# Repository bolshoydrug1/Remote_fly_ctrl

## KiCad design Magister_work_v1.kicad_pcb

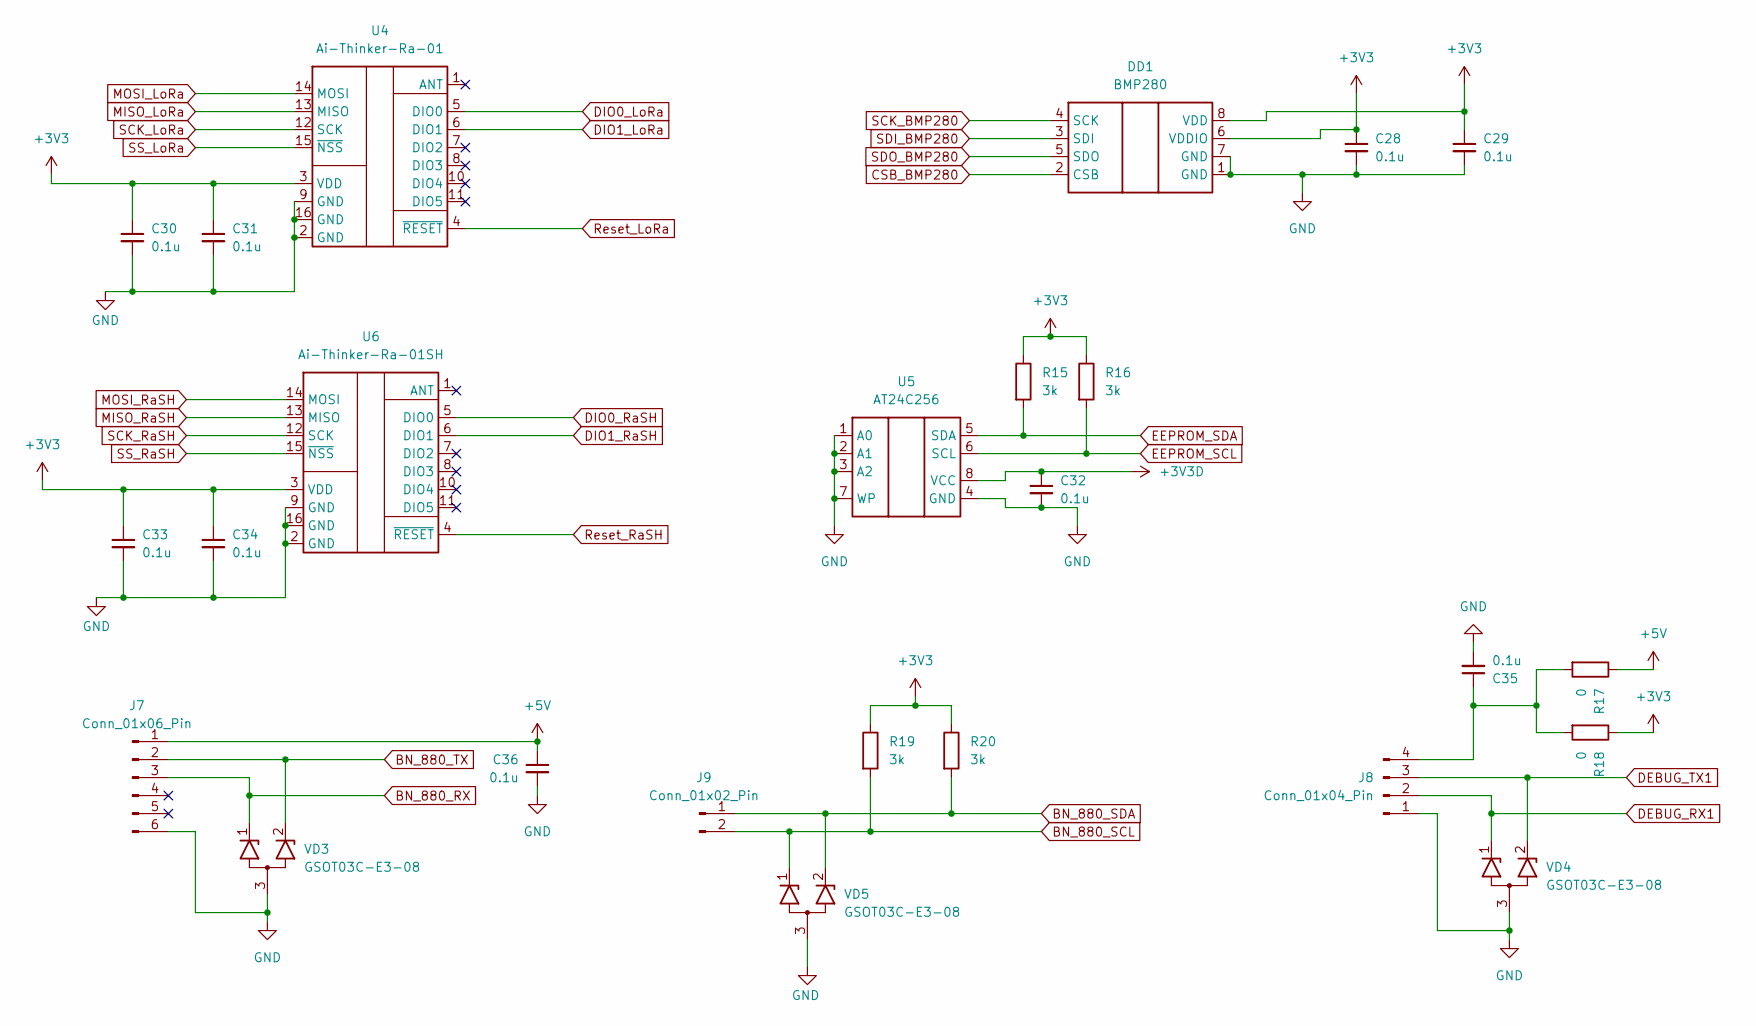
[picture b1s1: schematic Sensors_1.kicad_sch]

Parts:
C28, C29, C30, C31, C32, C33, C34, C35, C36: 0.1u; C_0805_2012Metric_Pad1.18x1.45mm_HandSolder
DD1: BMP280; Bosch_LGA-8_2x2.5mm_P0.65mm_ClockwisePinNumbering
J7: Conn_01x06_Pin; Hirose_DF13-06P-1.25DSA_1x06_P1.25mm_Vertical
J8: Conn_01x04_Pin; PinSocket_1x04_P2.54mm_Vertical
J9: Conn_01x02_Pin; Hirose_DF13-02P-1.25DSA_1x02_P1.25mm_Vertical
R15, R16, R19, R20: 3k; R_0805_2012Metric_Pad1.20x1.40mm_HandSolder
R17, R18: 0; R_0805_2012Metric_Pad1.20x1.40mm_HandSolder
U4: Ai-Thinker-Ra-01; Ai-Thinker-Ra-01-LoRa
U5: AT24C256; SOIC-8_3.9x4.9mm_P1.27mm
U6: Ai-Thinker-Ra-01SH; Ai-Thinker-Ra-01-LoRa
VD3, VD4, VD5: GSOT03C-E3-08; SOT-23

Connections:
+3V3: C28.1, C29.1, C30.1, C31.1, C32.1, C33.1, C34.1, DD1.6 (VDDIO), DD1.8 (VDD), R15.1, R16.1, R18.1, R19.1, R20.1, U4.3 (VDD), U5.8 (VCC), U6.3 (VDD); also elsewhere on the board
+5V: C36.1, J7.1, R17.1; also elsewhere on the board
BN_880_RX: J7.3, VD3.1 (K1); also elsewhere on the board
BN_880_SCL: J9.2, R19.2, VD5.1 (K1); also elsewhere on the board
BN_880_SDA: J9.1, R20.2, VD5.2 (K2); also elsewhere on the board
BN_880_TX: J7.2, VD3.2 (K2); also elsewhere on the board
CSB_BMP280: DD1.2 (CSB); also elsewhere on the board
DEBUG_RX1: J8.2, VD4.1 (K1); also elsewhere on the board
DEBUG_TX1: J8.3, VD4.2 (K2); also elsewhere on the board
DIO0_LoRa: U4.5 (DIO0); also elsewhere on the board
DIO0_RaSH: U6.5 (DIO0); also elsewhere on the board
DIO1_LoRa: U4.6 (DIO1); also elsewhere on the board
DIO1_RaSH: U6.6 (DIO1); also elsewhere on the board
EEPROM_SCL: R16.2, U5.6 (SCL); also elsewhere on the board
EEPROM_SDA: R15.2, U5.5 (SDA); also elsewhere on the board
GND: C28.2, C29.2, C30.2, C31.2, C32.2, C33.2, C34.2, C35.2, C36.2, DD1.1 (GND), DD1.7 (GND), J7.6, J8.1, U4.2 (GND), U4.9 (GND), U4.16 (GND), U5.1 (A0), U5.2 (A1), U5.3 (A2), U5.4 (GND), U5.7 (WP), U6.2 (GND), U6.9 (GND), U6.16 (GND), VD3.3 (A), VD4.3 (A), VD5.3 (A); also elsewhere on the board
MISO_LoRa: U4.13 (MISO); also elsewhere on the board
MISO_RaSH: U6.13 (MISO); also elsewhere on the board
MOSI_LoRa: U4.14 (MOSI); also elsewhere on the board
MOSI_RaSH: U6.14 (MOSI); also elsewhere on the board
unnamed: C35.1, J8.4, R17.2, R18.2
Reset_LoRa: U4.4 (~RESET); also elsewhere on the board
Reset_RaSH: U6.4 (~RESET); also elsewhere on the board
SCK_BMP280: DD1.4 (SCK); also elsewhere on the board
SCK_LoRa: U4.12 (SCK); also elsewhere on the board
SCK_RaSH: U6.12 (SCK); also elsewhere on the board
SDI_BMP280: DD1.3 (SDI); also elsewhere on the board
SDO_BMP280: DD1.5 (SDO); also elsewhere on the board
SS_LoRa: U4.15 (~NSS); also elsewhere on the board
SS_RaSH: U6.15 (~NSS); also elsewhere on the board

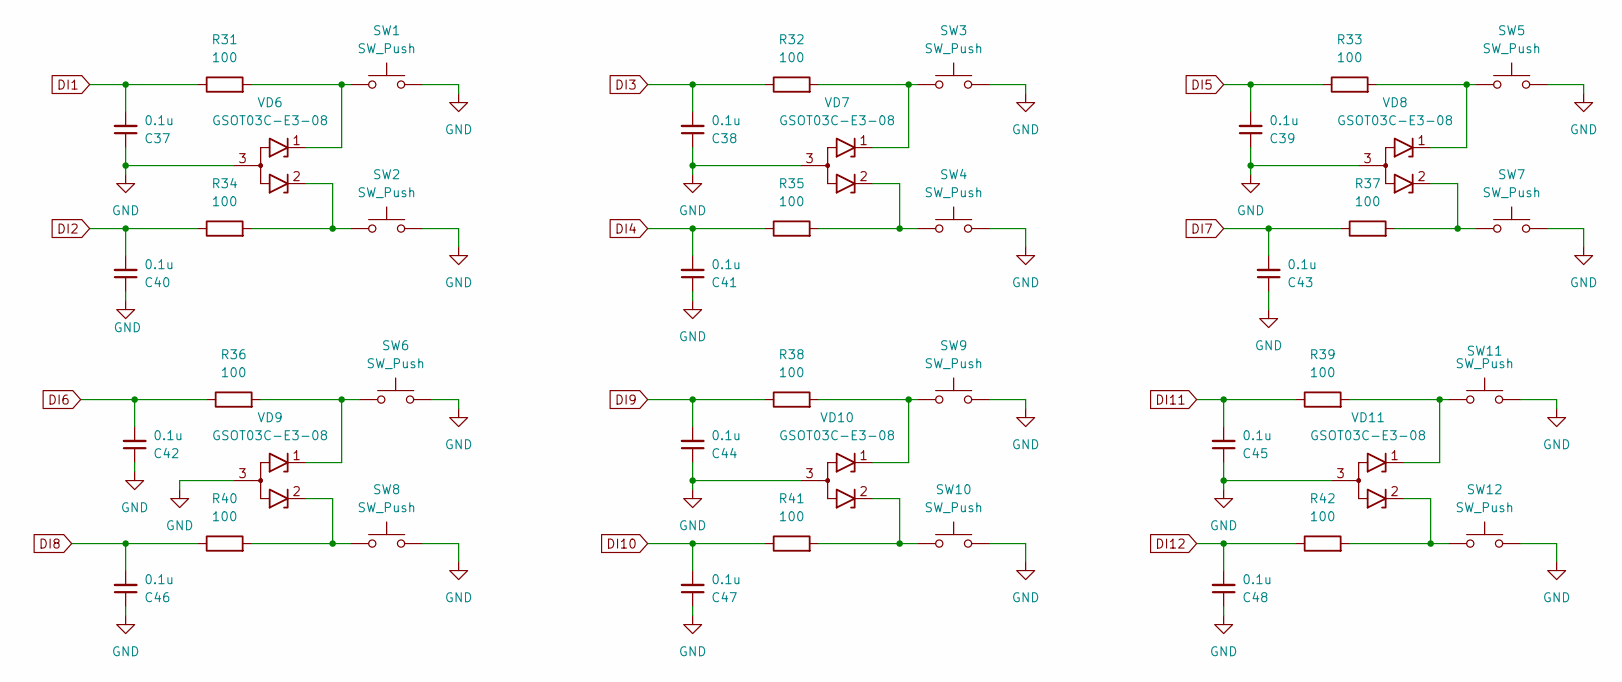
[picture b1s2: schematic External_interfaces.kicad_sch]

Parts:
C37, C38, C39, C40, C41, C42, C43, C44, C45, C46, C47, C48: 0.1u; C_0805_2012Metric_Pad1.18x1.45mm_HandSolder
R31, R32, R33, R34, R35, R36, R37, R38, R39, R40, R41, R42: 100; R_0805_2012Metric_Pad1.20x1.40mm_HandSolder
SW1, SW2, SW3, SW4, SW5, SW6, SW7, SW8, SW9, SW10, SW11, SW12: SW_Push; SW_PUSH_6mm
VD6, VD7, VD8, VD9, VD10, VD11: GSOT03C-E3-08; SOT-23

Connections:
DI1: C37.2, R31.1; also elsewhere on the board
DI2: C40.2, R34.1; also elsewhere on the board
DI3: C38.2, R32.1; also elsewhere on the board
DI4: C41.2, R35.1; also elsewhere on the board
DI5: C39.2, R33.1; also elsewhere on the board
DI6: C42.2, R36.1; also elsewhere on the board
DI7: C43.2, R37.1; also elsewhere on the board
DI8: C46.2, R40.1; also elsewhere on the board
DI9: C44.2, R38.1; also elsewhere on the board
DI10: C47.2, R41.1; also elsewhere on the board
DI11: C45.2, R39.1; also elsewhere on the board
DI12: C48.2, R42.1; also elsewhere on the board
GND: C37.1, C38.1, C39.1, C40.1, C41.1, C42.1, C43.1, C44.1, C45.1, C46.1, C47.1, C48.1, SW1.2, SW2.2, SW3.2, SW4.2, SW5.2, SW6.2, SW7.2, SW8.2, SW9.2, SW10.2, SW11.2, SW12.2, VD6.3 (A), VD7.3 (A), VD8.3 (A), VD9.3 (A), VD10.3 (A), VD11.3 (A); also elsewhere on the board
unnamed: R31.2, SW1.1, VD6.1 (K1)
unnamed: R34.2, SW2.1, VD6.2 (K2)
unnamed: R32.2, SW3.1, VD7.1 (K1)
unnamed: R35.2, SW4.1, VD7.2 (K2)
unnamed: R33.2, SW5.1, VD8.1 (K1)
unnamed: R37.2, SW7.1, VD8.2 (K2)
unnamed: R36.2, SW6.1, VD9.1 (K1)
unnamed: R40.2, SW8.1, VD9.2 (K2)
unnamed: R38.2, SW9.1, VD10.1 (K1)
unnamed: R41.2, SW10.1, VD10.2 (K2)
unnamed: R39.2, SW11.1, VD11.1 (K1)
unnamed: R42.2, SW12.1, VD11.2 (K2)

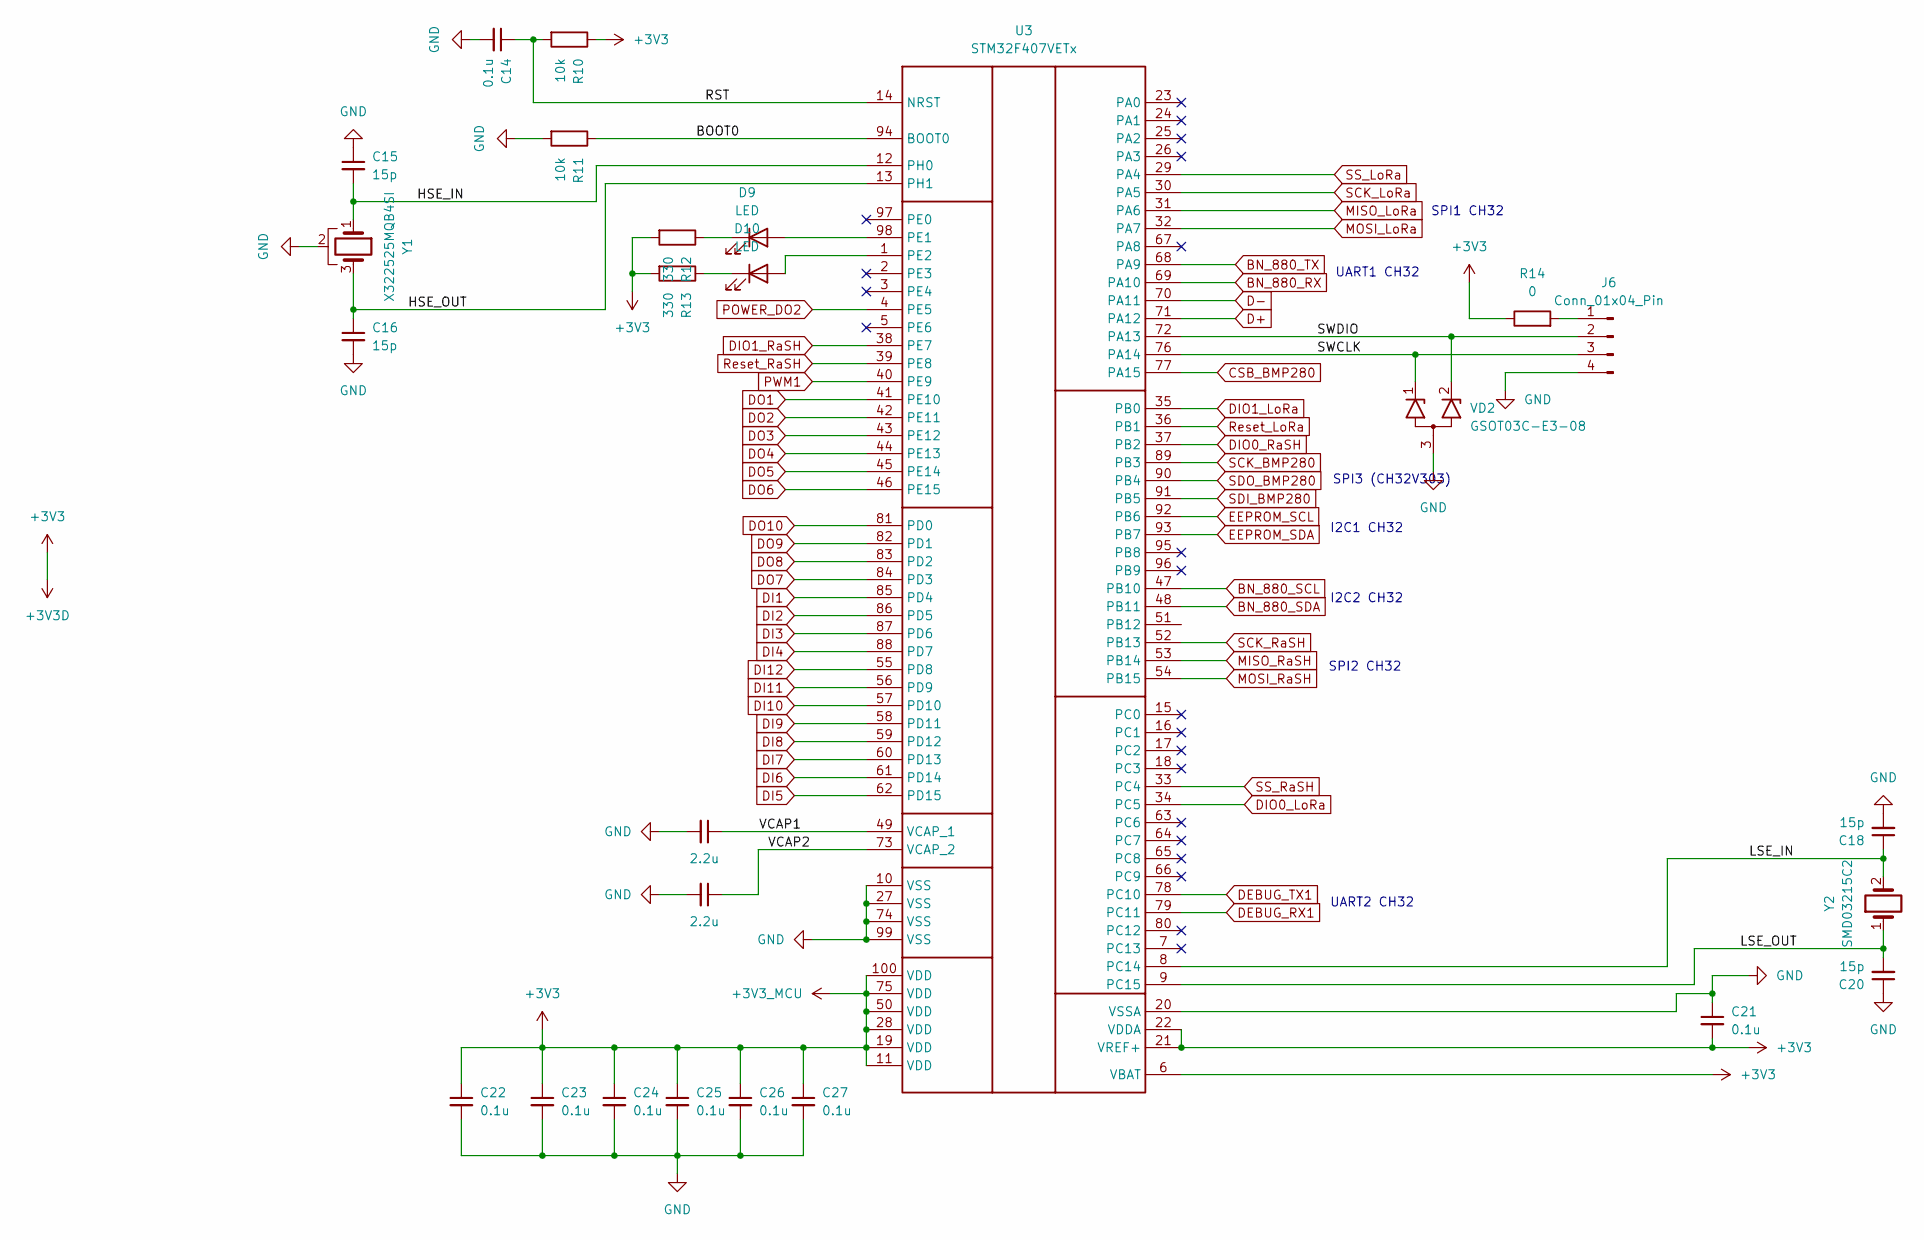
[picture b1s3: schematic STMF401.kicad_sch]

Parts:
C14, C21, C22, C23, C24, C25, C26, C27: 0.1u; C_0805_2012Metric_Pad1.18x1.45mm_HandSolder
C15, C16, C18, C20: 15p; C_0805_2012Metric_Pad1.18x1.45mm_HandSolder
C17, C19: 2.2u; C_0805_2012Metric_Pad1.18x1.45mm_HandSolder
D9, D10: LED; LED_0805_2012Metric_Pad1.15x1.40mm_HandSolder
J6: Conn_01x04_Pin; PinSocket_1x04_P2.54mm_Vertical
R10, R11: 10k; R_0805_2012Metric_Pad1.20x1.40mm_HandSolder
R12, R13: 330; R_0805_2012Metric_Pad1.20x1.40mm_HandSolder
R14: 0; R_0805_2012Metric_Pad1.20x1.40mm_HandSolder
U3: STM32F407VETx; LQFP-100_14x14mm_P0.5mm
VD2: GSOT03C-E3-08; SOT-23
Y1: X322525MQB4SI; Oscillator_SMD_Abracon_ASE-4Pin_3.2x2.5mm
Y2: SMD03215C2; Crystal_SMD_3215-2Pin_3.2x1.5mm

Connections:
+3V3: C21.2, C22.1, C23.1, C24.1, C25.1, C26.1, C27.1, R10.1, R12.2, R13.2, R14.1, U3.6 (VBAT), U3.11 (VDD), U3.19 (VDD), U3.21 (VREF+), U3.22 (VDDA), U3.28 (VDD), U3.50 (VDD), U3.75 (VDD), U3.100 (VDD); also elsewhere on the board
/STMF401_Sheet/BOOT0: R11.1, U3.94 (BOOT0)
/STMF401_Sheet/HSE_IN: C15.2, U3.12 (PH0), Y1.1 (OSC)
/STMF401_Sheet/HSE_OUT: C16.1, U3.13 (PH1), Y1.3 (OSC)
/STMF401_Sheet/LSE_IN: C18.1, U3.8 (PC14), Y2.2 (OSC)
/STMF401_Sheet/LSE_OUT: C20.2, U3.9 (PC15), Y2.1 (OSC)
/STMF401_Sheet/RST: C14.1, R10.2, U3.14 (NRST)
/STMF401_Sheet/SWCLK: J6.3, U3.76 (PA14), VD2.1 (K1)
/STMF401_Sheet/SWDIO: J6.2, U3.72 (PA13), VD2.2 (K2)
/STMF401_Sheet/VCAP1: C17.1, U3.49 (VCAP_1)
/STMF401_Sheet/VCAP2: C19.1, U3.73 (VCAP_2)
BN_880_RX: U3.69 (PA10); also elsewhere on the board
BN_880_SCL: U3.47 (PB10); also elsewhere on the board
BN_880_SDA: U3.48 (PB11); also elsewhere on the board
BN_880_TX: U3.68 (PA9); also elsewhere on the board
CSB_BMP280: U3.77 (PA15); also elsewhere on the board
D+: U3.71 (PA12); also elsewhere on the board
D-: U3.70 (PA11); also elsewhere on the board
DEBUG_RX1: U3.79 (PC11); also elsewhere on the board
DEBUG_TX1: U3.78 (PC10); also elsewhere on the board
DI1: U3.85 (PD4); also elsewhere on the board
DI2: U3.86 (PD5); also elsewhere on the board
DI3: U3.87 (PD6); also elsewhere on the board
DI4: U3.88 (PD7); also elsewhere on the board
DI5: U3.62 (PD15); also elsewhere on the board
DI6: U3.61 (PD14); also elsewhere on the board
DI7: U3.60 (PD13); also elsewhere on the board
DI8: U3.59 (PD12); also elsewhere on the board
DI9: U3.58 (PD11); also elsewhere on the board
DI10: U3.57 (PD10); also elsewhere on the board
DI11: U3.56 (PD9); also elsewhere on the board
DI12: U3.55 (PD8); also elsewhere on the board
DIO0_LoRa: U3.34 (PC5); also elsewhere on the board
DIO0_RaSH: U3.37 (PB2); also elsewhere on the board
DIO1_LoRa: U3.35 (PB0); also elsewhere on the board
DIO1_RaSH: U3.38 (PE7); also elsewhere on the board
DO1: U3.41 (PE10); also elsewhere on the board
DO2: U3.42 (PE11); also elsewhere on the board
DO3: U3.43 (PE12); also elsewhere on the board
DO4: U3.44 (PE13); also elsewhere on the board
DO5: U3.45 (PE14); also elsewhere on the board
DO6: U3.46 (PE15); also elsewhere on the board
DO7: U3.84 (PD3); also elsewhere on the board
DO8: U3.83 (PD2); also elsewhere on the board
DO9: U3.82 (PD1); also elsewhere on the board
DO10: U3.81 (PD0); also elsewhere on the board
EEPROM_SCL: U3.92 (PB6); also elsewhere on the board
EEPROM_SDA: U3.93 (PB7); also elsewhere on the board
GND: C14.2, C15.1, C16.2, C17.2, C18.2, C19.2, C20.1, C21.1, C22.2, C23.2, C24.2, C25.2, C26.2, C27.2, J6.4, R11.2, U3.10 (VSS), U3.20 (VSSA), U3.27 (VSS), U3.74 (VSS), U3.99 (VSS), VD2.3 (A), Y1.2 (GND), Y1.4 (GND); also elsewhere on the board
MISO_LoRa: U3.31 (PA6); also elsewhere on the board
MISO_RaSH: U3.53 (PB14); also elsewhere on the board
MOSI_LoRa: U3.32 (PA7); also elsewhere on the board
MOSI_RaSH: U3.54 (PB15); also elsewhere on the board
unnamed: D9.2 (A), U3.98 (PE1)
unnamed: D9.1 (K), R12.1
unnamed: D10.2 (A), U3.1 (PE2)
unnamed: D10.1 (K), R13.1
unnamed: J6.1, R14.2
POWER_DO2: U3.4 (PE5); also elsewhere on the board
PWM1: U3.40 (PE9); also elsewhere on the board
Reset_LoRa: U3.36 (PB1); also elsewhere on the board
Reset_RaSH: U3.39 (PE8); also elsewhere on the board
SCK_BMP280: U3.89 (PB3); also elsewhere on the board
SCK_LoRa: U3.30 (PA5); also elsewhere on the board
SCK_RaSH: U3.52 (PB13); also elsewhere on the board
SDI_BMP280: U3.91 (PB5); also elsewhere on the board
SDO_BMP280: U3.90 (PB4); also elsewhere on the board
SS_LoRa: U3.29 (PA4); also elsewhere on the board
SS_RaSH: U3.33 (PC4); also elsewhere on the board

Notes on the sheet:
SPI1 CH32
SPI3 (CH32V303)
SPI2 CH32
I2C1 CH32
UART1 CH32
UART2 CH32
I2C2 CH32

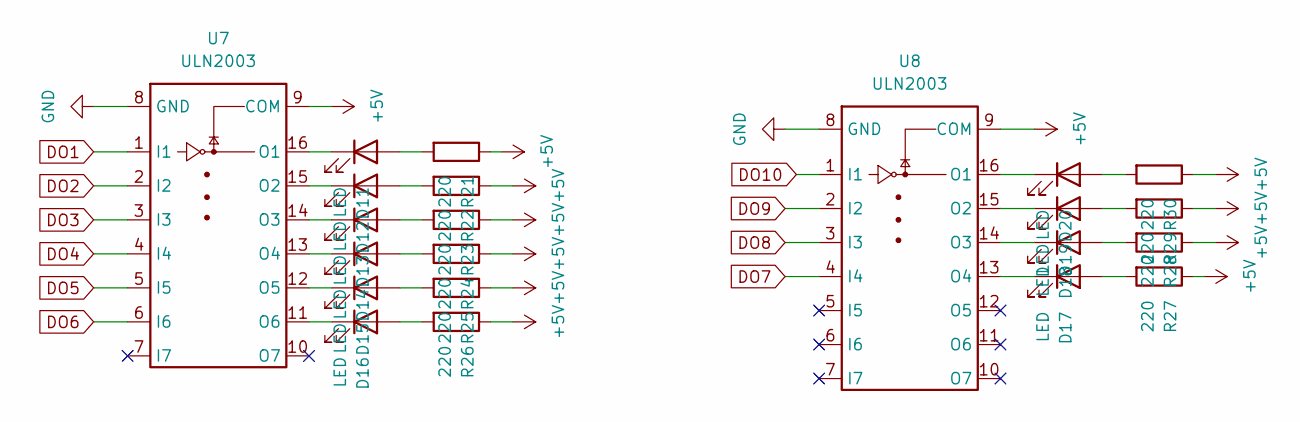
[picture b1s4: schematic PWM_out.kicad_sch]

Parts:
D11, D12, D13, D14, D15, D16, D17, D18, D19, D20: LED; LED_D3.0mm
R21, R22, R23, R24, R25, R26, R27, R28, R29, R30: 220; R_0805_2012Metric_Pad1.20x1.40mm_HandSolder
U7, U8: ULN2003; SO-16_3.9x9.9mm_P1.27mm

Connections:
+5V: R21.1, R22.1, R23.1, R24.1, R25.1, R26.1, R27.1, R28.1, R29.1, R30.1, U7.9 (COM), U8.9 (COM); also elsewhere on the board
DO1: U7.1 (I1); also elsewhere on the board
DO2: U7.2 (I2); also elsewhere on the board
DO3: U7.3 (I3); also elsewhere on the board
DO4: U7.4 (I4); also elsewhere on the board
DO5: U7.5 (I5); also elsewhere on the board
DO6: U7.6 (I6); also elsewhere on the board
DO7: U8.4 (I4); also elsewhere on the board
DO8: U8.3 (I3); also elsewhere on the board
DO9: U8.2 (I2); also elsewhere on the board
DO10: U8.1 (I1); also elsewhere on the board
GND: U7.8 (GND), U8.8 (GND); also elsewhere on the board
unnamed: D11.2 (A), R21.2
unnamed: D11.1 (K), U7.16 (O1)
unnamed: D12.2 (A), R22.2
unnamed: D12.1 (K), U7.15 (O2)
unnamed: D13.2 (A), R23.2
unnamed: D13.1 (K), U7.14 (O3)
unnamed: D14.2 (A), R24.2
unnamed: D14.1 (K), U7.13 (O4)
unnamed: D15.2 (A), R25.2
unnamed: D15.1 (K), U7.12 (O5)
unnamed: D16.2 (A), R26.2
unnamed: D16.1 (K), U7.11 (O6)
unnamed: D17.2 (A), R27.2
unnamed: D17.1 (K), U8.13 (O4)
unnamed: D18.2 (A), R28.2
unnamed: D18.1 (K), U8.14 (O3)
unnamed: D19.2 (A), R29.2
unnamed: D19.1 (K), U8.15 (O2)
unnamed: D20.2 (A), R30.2
unnamed: D20.1 (K), U8.16 (O1)

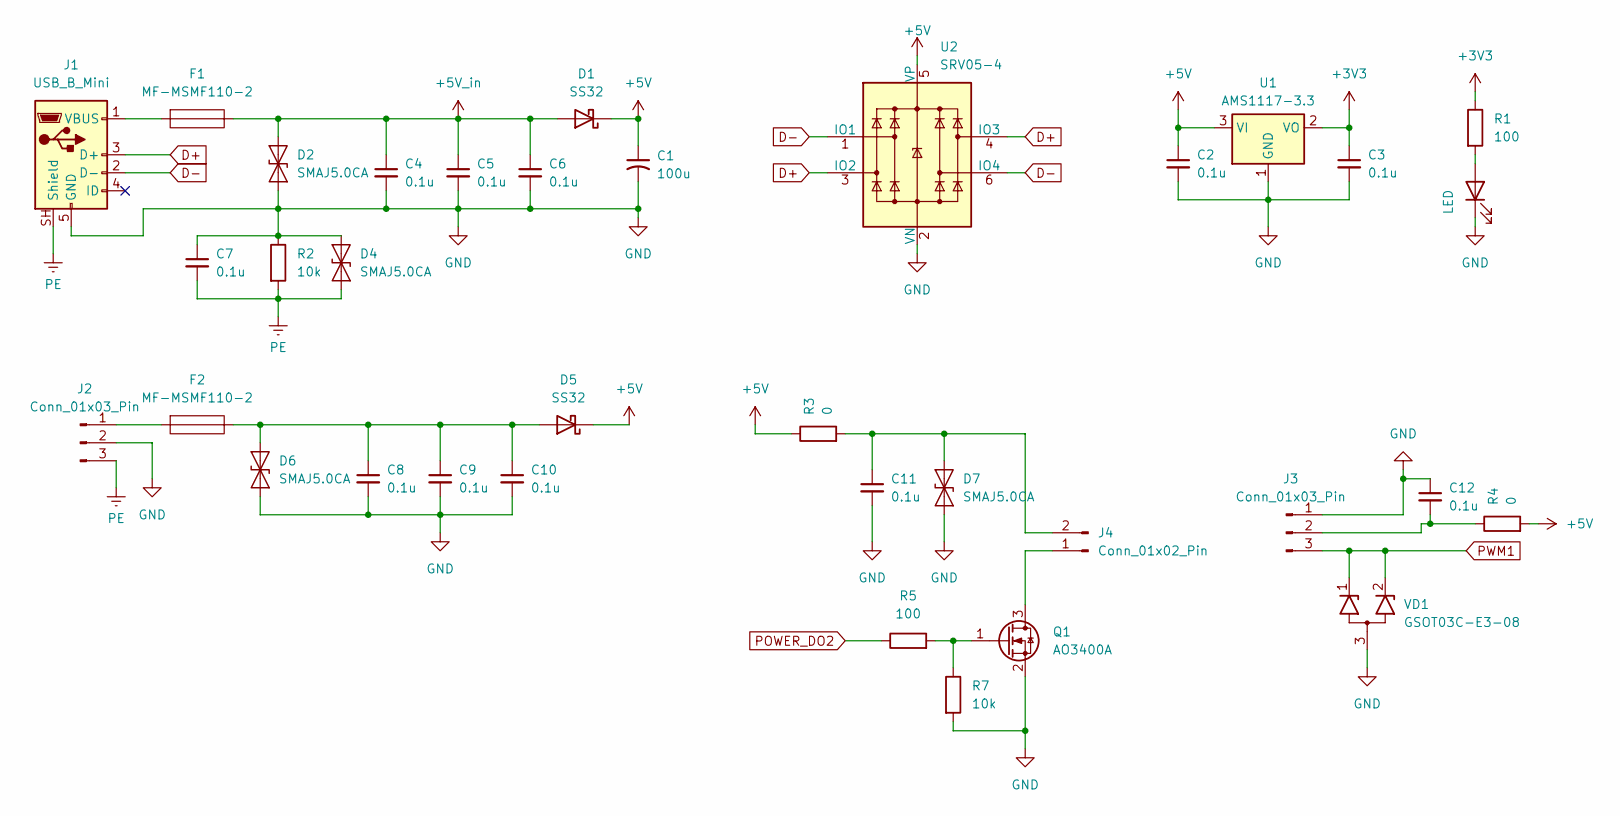
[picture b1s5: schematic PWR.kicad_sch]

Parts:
C1: 100u; C_Elec_6.3x7.7
C2, C3, C4, C5, C6, C7, C8, C9, C10, C11, C12: 0.1u; C_0805_2012Metric_Pad1.18x1.45mm_HandSolder
D1, D5: SS32; D_SMA
D2, D4, D6, D7: SMAJ5.0CA; D_SMA
D3: LED; LED_D3.0mm_Clear
F1, F2: MF-MSMF110-2; Fuse_1812_4532Metric_Pad1.30x3.40mm_HandSolder
J1: USB_B_Mini; USB_Mini-B_Lumberg_2486_01_Horizontal
J2: Conn_01x03_Pin; JST_NV_B03P-NV_1x03_P5.00mm_Vertical
J3: Conn_01x03_Pin; PinHeader_1x03_P2.54mm_Vertical
J4: Conn_01x02_Pin; PinHeader_1x02_P2.54mm_Vertical
Q1: AO3400A; SOT-23
R1, R5: 100; R_0805_2012Metric_Pad1.20x1.40mm_HandSolder
R2, R7: 10k; R_0805_2012Metric_Pad1.20x1.40mm_HandSolder
R3, R4: 0; R_0805_2012Metric_Pad1.20x1.40mm_HandSolder
U1: AMS1117-3.3; SOT-223-3_TabPin2
U2: SRV05-4; SOT-23-6
VD1: GSOT03C-E3-08; SOT-23

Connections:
+3V3: C3.1, R1.1, U1.2 (VO); also elsewhere on the board
+5V: C1.1, C2.1, D1.1 (K), D5.1 (K), R3.1, R4.2, U1.3 (VI), U2.5 (VP); also elsewhere on the board
+5V_in: C4.1, C5.1, C6.1, D1.2 (A), D2.2 (A2), F1.2 (A2)
D+: J1.3 (D+), U2.3 (IO2), U2.4 (IO3); also elsewhere on the board
D-: J1.2 (D-), U2.1 (IO1), U2.6 (IO4); also elsewhere on the board
GND: C1.2, C2.2, C3.2, C4.2, C5.2, C6.2, C7.1, C8.2, C9.2, C10.2, C11.2, C12.1, D2.1 (A1), D3.1 (K), D4.2 (A2), D6.1 (A1), D7.1 (A1), J1.5 (GND), J2.2, J3.1, Q1.2 (S), R2.1, R7.2, U1.1 (GND), U2.2 (VN), VD1.3 (A); also elsewhere on the board
unnamed: D3.2 (A), R1.2
unnamed: C8.1, C9.1, C10.1, D5.2 (A), D6.2 (A2), F2.2 (A2)
unnamed: C11.1, D7.2 (A2), J4.2, R3.2
unnamed: F1.1 (A1), J1.1 (VBUS)
unnamed: F2.1 (A1), J2.1
unnamed: C12.2, J3.2, R4.1
unnamed: J4.1, Q1.3 (D)
unnamed: Q1.1 (G), R5.2, R7.1
PE: C7.2, D4.1 (A1), J1.SH (Shield), J2.3, R2.2
POWER_DO2: R5.1; also elsewhere on the board
PWM1: J3.3, VD1.1 (K1), VD1.2 (K2); also elsewhere on the board

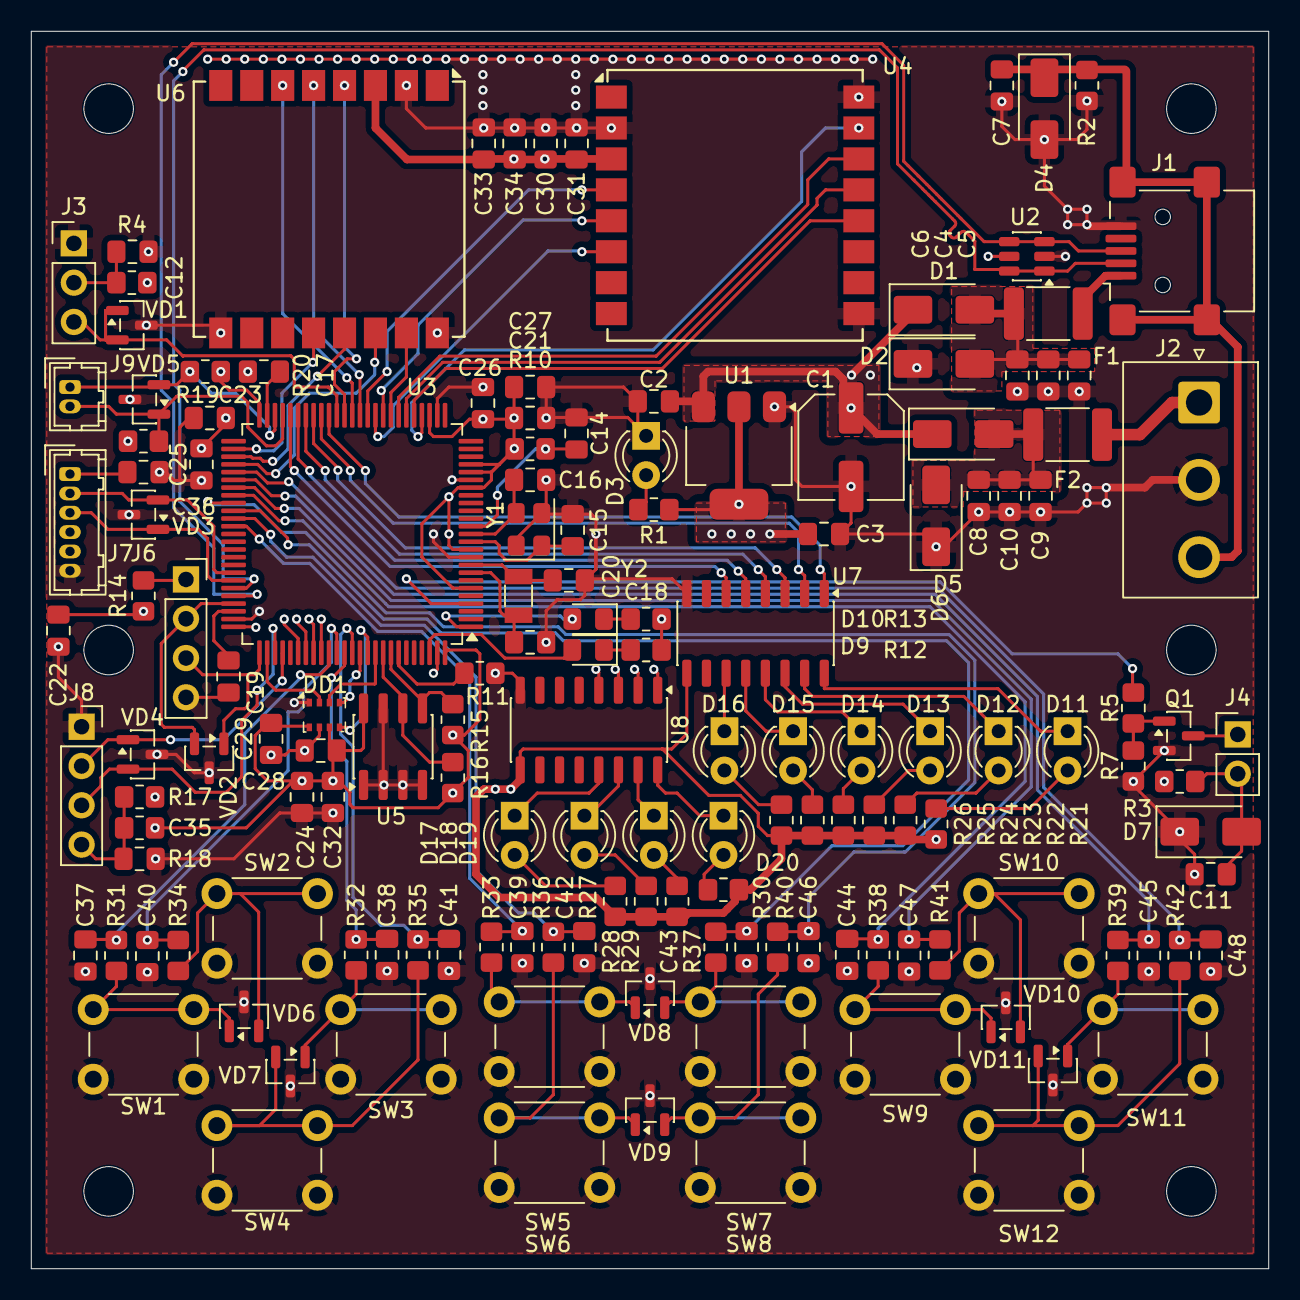
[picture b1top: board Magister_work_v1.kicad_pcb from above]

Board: 4 copper layers, 80.0 x 80.0 mm, 150 parts (0 on the bottom side), 113 nets.

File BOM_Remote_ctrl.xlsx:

Reference | Qty | Value | DNP | Exclude from BOM | Exclude from Board | Footprint | Datasheet
C1 | 1 | 100u |  |  |  | Capacitor_SMD:C_Elec_6.3x7.7
C2,C3,C4,C5,C6,C7,C8,C9,C10,C11,C12,C14,C21,C22,C23,C24,C25,C26,C27,C28,C29,C30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 | 40 | 0.1u |  |  |  | Capacitor_SMD:C_0805_2012Metric_Pad1.18x1.45mm_HandSolder
C15,C16,C18,C20 | 4 | 15p |  |  |  | Capacitor_SMD:C_0805_2012Metric_Pad1.18x1.45mm_HandSolder
C17,C19 | 2 | 2.2u |  |  |  | Capacitor_SMD:C_0805_2012Metric_Pad1.18x1.45mm_HandSolder
D1,D5 | 2 | SS32 |  |  |  | Diode_SMD:D_SMA | https://www.vishay.com/docs/88751/ss32.pdf
D2,D4,D6,D7 | 4 | SMAJ5.0CA |  |  |  | Diode_SMD:D_SMA | https://www.littelfuse.com/media?resourcetype=datasheets&ite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
D3 | 1 | LED |  |  |  | LED_THT:LED_D3.0mm_Clear
D9,D10 | 2 | LED |  |  |  | LED_SMD:LED_0805_2012Metric_Pad1.15x1.40mm_HandSolder
D11,D12,D13,D14,D15,D16,D17,D18,D19,D20 | 10 | LED |  |  |  | LED_THT:LED_D3.0mm
DD1 | 1 | BMP280 |  |  |  | Package_LGA:Bosch_LGA-8_2x2.5mm_P0.65mm_ClockwisePinNumbering | https://ae-bst.resource.bosch.com/media/_tech/media/datashee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
F1,F2 | 2 | MF-MSMF110-2 |  |  |  | Fuse:Fuse_1812_4532Metric_Pad1.30x3.40mm_HandSolder
J1 | 1 | USB_B_Mini |  |  |  | Connector_USB:USB_Mini-B_Lumberg_2486_01_Horizontal
J2 | 1 | Conn_01x03_Pin |  |  |  | Connector_JST:JST_NV_B03P-NV_1x03_P5.00mm_Vertical
J3 | 1 | Conn_01x03_Pin |  |  |  | Connector_PinHeader_2.54mm:PinHeader_1x03_P2.54mm_Vertical | do not install !!!
J4 | 1 | Conn_01x02_Pin |  |  |  | Connector_PinHeader_2.54mm:PinHeader_1x02_P2.54mm_Vertical | do not install !!!
J6,J8 | 2 | Conn_01x04_Pin |  |  |  | Connector_PinSocket_2.54mm:PinSocket_1x04_P2.54mm_Vertical
J7 | 1 | Conn_01x06_Pin |  |  |  | Connector_Hirose:Hirose_DF13-06P-1.25DSA_1x06_P1.25mm_Vertical
J9 | 1 | Conn_01x02_Pin |  |  |  | Connector_Hirose:Hirose_DF13-02P-1.25DSA_1x02_P1.25mm_Vertical
Q1 | 1 | AO3400A |  |  |  | Package_TO_SOT_SMD:SOT-23 | http://www.aosmd.com/pdfs/datasheet/AO3400A.pdf
R1,R5,R31,R32,R33,R34,R35,R36,R37,R38,R39,R40,R41,R42 | 14 | 100 |  |  |  | Resistor_SMD:R_0805_2012Metric_Pad1.20x1.40mm_HandSolder
R2,R7,R10,R11 | 4 | 10k |  |  |  | Resistor_SMD:R_0805_2012Metric_Pad1.20x1.40mm_HandSolder
R3,R4,R14,R17,R18 | 5 | 0 |  |  |  | Resistor_SMD:R_0805_2012Metric_Pad1.20x1.40mm_HandSolder
R12,R13 | 2 | 330 |  |  |  | Resistor_SMD:R_0805_2012Metric_Pad1.20x1.40mm_HandSolder
R15,R16,R19,R20 | 4 | 3k |  |  |  | Resistor_SMD:R_0805_2012Metric_Pad1.20x1.40mm_HandSolder
R21,R22,R23,R24,R25,R26,R27,R28,R29,R30 | 10 | 220 |  |  |  | Resistor_SMD:R_0805_2012Metric_Pad1.20x1.40mm_HandSolder
SW1,SW2,SW3,SW4,SW5,SW6,SW7,SW8,SW9,SW10,SW11,SW12 | 12 | SW_Push |  |  |  | Button_Switch_THT:SW_PUSH_6mm
U1 | 1 | AMS1117-3.3 |  |  |  | Package_TO_SOT_SMD:SOT-223-3_TabPin2 | http://www.advanced-monolithic.com/pdf/ds1117.pdf
U2 | 1 | SRV05-4 |  |  |  | Package_TO_SOT_SMD:SOT-23-6 | http://www.onsemi.com/pub/Collateral/SRV05-4-D.PDF
U3 | 1 | CH32V303VCT6 |  |  |  | Package_QFP:LQFP-100_14x14mm_P0.5mm | https://static.chipdip.ru/lib/164/DOC045164022.pdf
U4 | 1 | Ai-Thinker-Ra-01 |  |  |  | RF_Module:Ai-Thinker-Ra-01-LoRa | http://wiki.ai-thinker.com/_media/lora/docs/c047ps01a1_ra-01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
U5 | 1 | AT24C256 |  |  |  | Package_SO:SOIC-8_3.9x4.9mm_P1.27mm | https://www.onsemi.cn/PowerSolutions/document/CAT24C256-D.PDF
U6 | 1 | Ai-Thinker-Ra-01SH |  |  |  | RF_Module:Ai-Thinker-Ra-01-LoRa | http://wiki.ai-thinker.com/_media/lora/docs/c047ps01a1_ra-01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
U7,U8 | 2 | ULN2003 |  |  |  | Package_SO:SO-16_3.9x9.9mm_P1.27mm | http://www.ti.com/lit/ds/symlink/uln2003a.pdf
VD1,VD2,VD3,VD4,VD5,VD6,VD7,VD8,VD9,VD10,VD11 | 11 | GSOT03C-E3-08 |  |  |  | Package_TO_SOT_SMD:SOT-23 | https://www.chipdip.ru/product/gsot03c-e3-08-ustroystvo-zasc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
Y1 | 1 | X322525MQB4SI |  |  |  | Oscillator:Oscillator_SMD_Abracon_ASE-4Pin_3.2x2.5mm | https://cdn.promelec.ru/upload/items/2023/03/10/YSX321SL.pdf
Y2 | 1 | SMD03215C2 |  |  |  | Crystal:Crystal_SMD_3215-2Pin_3.2x1.5mm | https://www.chipdip.ru/product/kvartsevyy-rezonator-32.768-k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
